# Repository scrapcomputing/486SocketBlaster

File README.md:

# Go back to the main branch. [Theres nothing to see here.](https://youtu.be/NuAKnbIr6TE)

# 486SocketBlaster

486SocketBlaster is a simple voltage adapter for 486 processors. It allows you
to use a 3-volt 486 CPU on an older 5-volt-only motherboard. For example you
can use a DX4 or an Am5x86 on an old 486 motherboard that would normally only
work with 5-volt CPUs. This basically converts any 3-volt CPU to an "Overdrive".

# How does it work ?

It is really simple: All CPU pins are passed through to the motherboard socket,
except for the Vcc. Those are connected to the output of a mini buck converter
that can be soldered to the 486SocketBlaster board.

# Soldering/Assembly Instructions

This board is not the easiest thing to solder, but can be done with a standard
soldering iron and some patience.
The best way to solder the headers is to start with the innermost one and work
outwards in a spiral manner alternating between the top and bottom side as
needed (see image below). This way you only work on the outside and can easily
reach all the pins.

A desoldering gun may be useful when you accidentally clog up other holes. But
it is probably best to be very careful and avoid clogging them in the first
place. Also using flux makes it easier.

Please make sure you check the solder joints (also check for continuity) before
you add another row of headers on the same side, because the new row will
permanently block your access to the solder joints!
Desoldering a header is almost impossible even with a desoldering gun due to the
very tight hole tolerances.
So it has to be soldered correctly from the first try.

# Voltage regulator

The 486SocketBlaster can be powered by a cheap of-the-shelf buck converter, or
by an external one. The circuit board accepts two common types of small voltage
buck converters, usually found using keywords like "mini buck converter".
These are commonly rated at up to 3A of current. Given that 3-volt 486 CPUs are
usually very efficient (the DX4-100 is rated at max 3.55/5.22W typical/max) such
a regulator should be adequate in most cases.
For best stability try to source a good quality part.

If you are planning to overclock or to use a more power hungry CPU, please use an external regulation circuit plugged in to the `ExtPwr` header, or use a *very* good quality mini buck converter.

# WARNING!!!

Please make sure you know what you are doing!
Improper assembly/settings/use can damage both your precious motherboard and your precious CPU!

# Features

- External Power Header. This can be used either for monitoring the CPU voltage, or for providing power externally, either with an external power supply or an external voltage regulator.
- CLKMUL Header for selecting/overriding the CPU multiplier. This controls CPU pin `R17`. 1-2 connects it to the motherboard socket pin and 2-3 connects it to ground. This reduces the multiplier of a DX4 to 2x (66MHz) and sets the multiplier of an Am5x86 to 4x (133MHz).
- WB/WT Header for selecting/overriding Write-Back/Write-Through cache. This controls processor CPU pin `B13` (which is the `CLKMUL` pin in earlier 486 CPUs). 1-2 connects it to the motherboard socket pin, and 2-3 connects it to Vcc, which enables Write-Back.

# Bill of materials

Item                            | ##  | Description
--------------------------------|-----|--------------------------------------------------------
mini buck converter             | 1   | We support two common sizes: 22x17mm and 18x12mm. These usually have chips like MP1584, MP2307 and others
40pin SIP pin header (male)     | 5   | Single-row round pin 2.54mm pitch (male). Socket pin diameter: 0.50mm, PCB pin diameter: 0.60mm. (see photo below)
40pin SIP socket header (female)| 5   | Single-row round pin sockets, 2.54mm pitch. PCB pin diameter: 0.55mm. (see photo below) 
SMD Ceramic Capacitors          | 4   | 10uF SMD 1206, 6.3V or higher
Through-hole Capacitor          | 1   | 10uF ceramic through-hole capacitor, 6.3V or higher
3-pin header 2.54mm pitch       | 2   | (optional) Headers used for selecting the CPU Multiplier (CLKMUL) and Write-Back/Write-Through cache (WB/WT)
Jumper 2.54mm pitch             | 2   | (optional) Jumpers for the CLKMUL and WB/WT headers

Gerber files can be found in the releases: https://github.com/scrapcomputing/486SocketBlaster/releases

Please note that the headers are a very tight fit. So please make sure that you get headers of the correct pin diameter.

With the limited testing I have done so far, it seems that you need at least
one 10uF through-hole ceramic capacitor, otherwise the voltage ripple is too
high and the system can become unstable with a DX4 @ 100MHz, using a cheap
MP1584-based buck converter.

# Videos featuring the 486 Socket Blaster
- Original video with rev0.1 PCB (part 1): https://www.youtube.com/watch?v=n5qlx4qKbSE
- Rev0.2 PCB and trying out smoothing caps (part 2): https://www.youtube.com/watch?v=7anzRWXtba0
- Choosing capacitor values for a 5x86 (part 3): https://www.youtube.com/watch?v=CLPSJ0jOQsU
- Detailed assembly instructions by Epictronics (rev 0.4 PCB): https://www.youtube.com/watch?v=vEpAoVE4KjU

# Changelist
- Rev 0.5 : Adds WB/WT header and fixes CLKMUL table silkscreen for am5x86.
- Rev 0.4 : Larger holes for the female headers (0.62mm instead of 0.57mm). These should fit headers with 0.55mm pin diameter.
- Rev 0.3 : Updates silk screen for larger capacitor values and fixes CLKMUL table.
- Rev 0.2 : Fixes initial revision bugs.

# List of other similar 486 adapter projects
- With an onboard voltage regulator: https://github.com/LimeProgramming/486SocketBlaster/tree/4-layer-onboard-regulator

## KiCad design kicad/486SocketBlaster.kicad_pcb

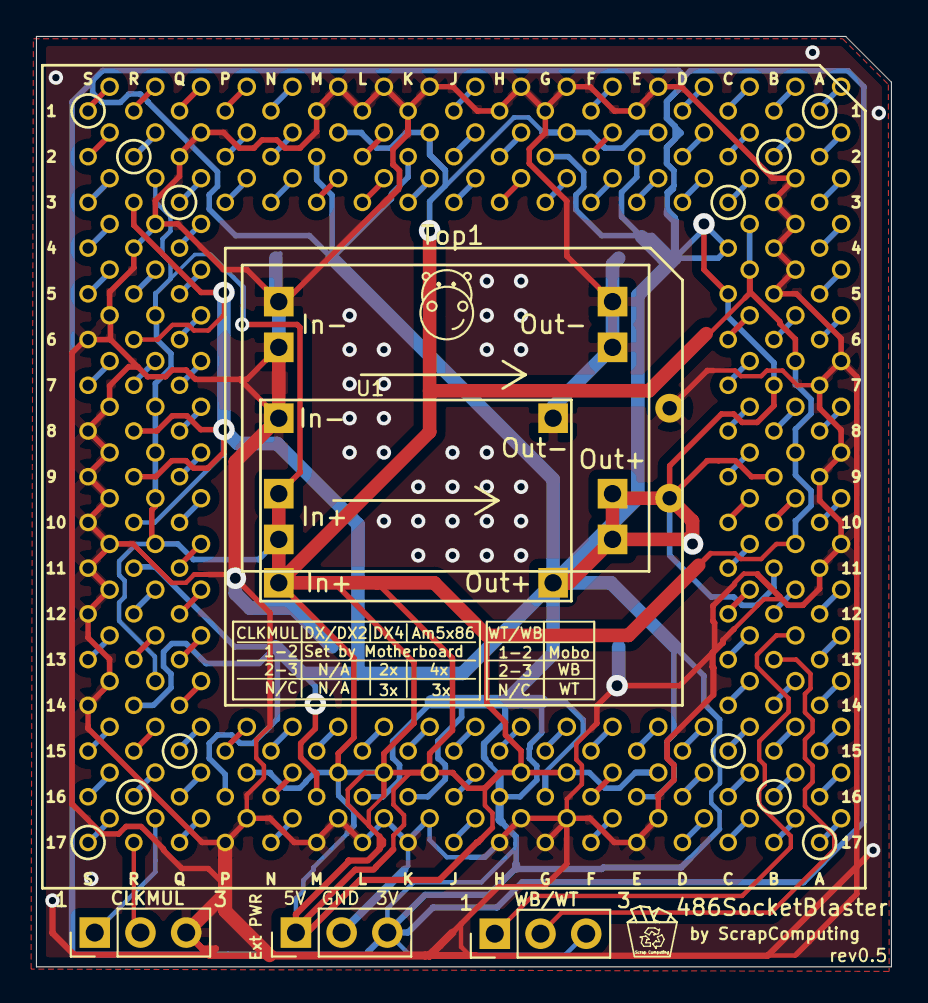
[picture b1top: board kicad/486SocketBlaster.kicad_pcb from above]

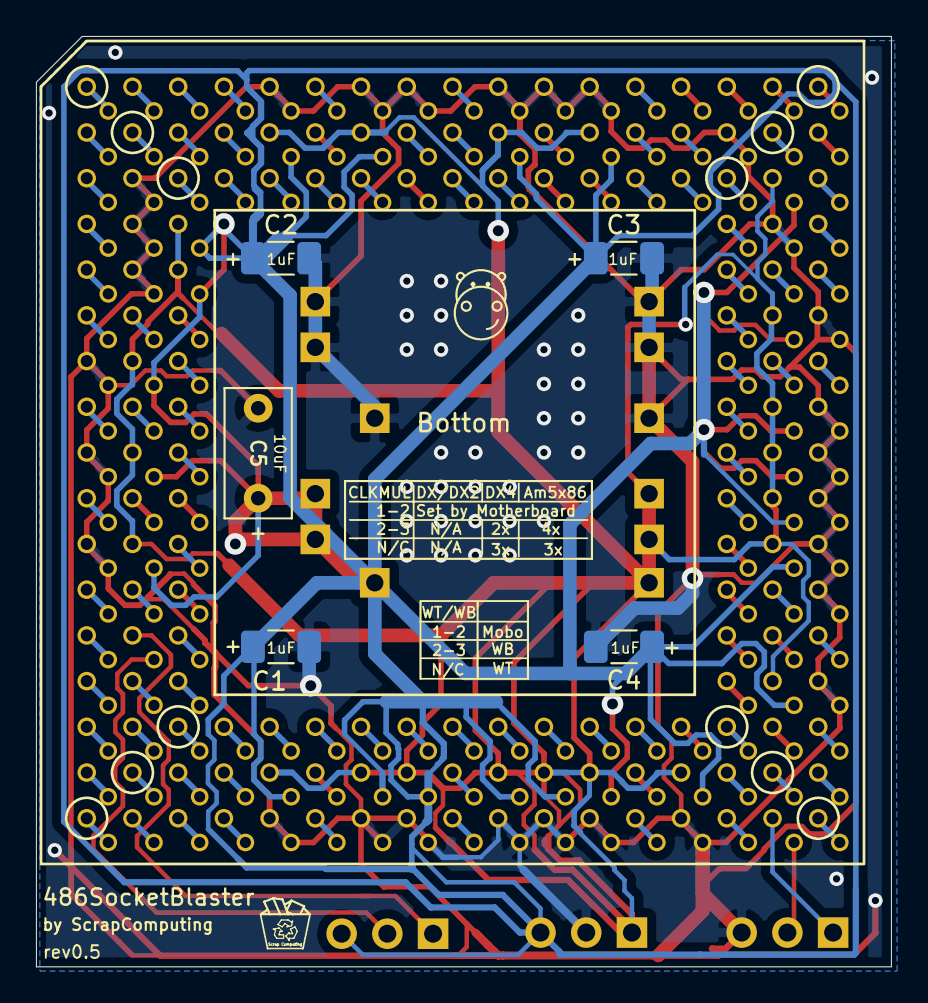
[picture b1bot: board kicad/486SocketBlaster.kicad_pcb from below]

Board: 2 copper layers, 47.5 x 51.7 mm, 12 parts (5 on the bottom side), 122 nets.

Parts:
Bot1: 486; 486_168pga
C1, C2, C3, C4: 10uF; C_1206_3216Metric_Pad1.33x1.80mm_HandSolder
C5: 10uF; C_Rect_L7.0mm_W3.5mm_P5.00mm
CLKMUL: CLKMUL; PinHeader_1x03_P2.54mm_Vertical
ExtPwr1: Conn_01x03; PinHeader_1x03_P2.54mm_Vertical
J1: Conn_01x03; PinHeader_1x03_P2.54mm_Vertical
Top1: 486; 486_168pga_socket
U1: VoltageRegulator; VoltageRegulator2
U3: VoltageRegulator

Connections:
GND: Bot1.A7, Bot1.A9, Bot1.A11, Bot1.B3, Bot1.B4, Bot1.B5, Bot1.E1, Bot1.E17, Bot1.G1, Bot1.G17, Bot1.H1, Bot1.H17, Bot1.K1, Bot1.K17, Bot1.L1, Bot1.L17, Bot1.M1, Bot1.M17, Bot1.P17, Bot1.Q2, Bot1.R4, Bot1.S6, Bot1.S8, Bot1.S9, Bot1.S10, Bot1.S11, Bot1.S12, Bot1.S14, C1.2, C2.2, C3.2, C4.2, C5.2, CLKMUL.3, ExtPwr1.2, Top1.A7, Top1.A9, Top1.A11, Top1.B3, Top1.B4, Top1.B5, Top1.E1, Top1.E17, Top1.G1, Top1.G17, Top1.H1, Top1.H17, Top1.K1, Top1.K17, Top1.L1, Top1.L17, Top1.M1, Top1.M17, Top1.P17, Top1.Q2, Top1.R4, Top1.S6, Top1.S8, Top1.S9, Top1.S10, Top1.S11, Top1.S12, Top1.S14, U1.GNDin, U1.GNDout, U3.GNDin, U3.GNDout
unnamed: Bot1.A1, Top1.A1
unnamed: Bot1.A2, Top1.A2
unnamed: Bot1.A3, Top1.A3
unnamed: Bot1.A4, Top1.A4
unnamed: Bot1.A5, Top1.A5
unnamed: Bot1.A6, Top1.A6
unnamed: Bot1.A8, Top1.A8
unnamed: Bot1.A10, Top1.A10
unnamed: Bot1.A12, Top1.A12
unnamed: Bot1.A13, Top1.A13
unnamed: Bot1.A14, Top1.A14
unnamed: Bot1.A15, Top1.A15
unnamed: Bot1.A16, Top1.A16
unnamed: Bot1.A17, Top1.A17
unnamed: Bot1.B1, Top1.B1
unnamed: Bot1.B2, Top1.B2
unnamed: Bot1.B6, Top1.B6
unnamed: Bot1.B8, Top1.B8
unnamed: Bot1.B10, Top1.B10
unnamed: Bot1.B7, Bot1.B9, Bot1.B11, Bot1.C4, Bot1.C5, Bot1.E2, Bot1.E16, Bot1.G2, Bot1.G16, Bot1.H16, Bot1.K2, Bot1.K16, Bot1.L16, Bot1.M2, Bot1.M16, Bot1.P16, Bot1.R3, Bot1.R6, Bot1.R8, Bot1.R9, Bot1.R10, Bot1.R11, Bot1.R14, ExtPwr1.1, U1.Vin, U3.Vin
unnamed: Bot1.B12, Top1.B12
unnamed: Bot1.B13, J1.1
unnamed: Bot1.B14, Top1.B14
unnamed: Bot1.B15, Top1.B15
unnamed: Bot1.B16, Top1.B16
unnamed: Bot1.B17, Top1.B17
unnamed: Bot1.C1, Top1.C1
unnamed: Bot1.C2, Top1.C2
unnamed: Bot1.C3, Top1.C3
unnamed: Bot1.C6, Top1.C6
unnamed: Bot1.C7, Top1.C7
unnamed: Bot1.C8, Top1.C8
unnamed: Bot1.C9, Top1.C9
unnamed: Bot1.C10, Top1.C10
unnamed: Bot1.C11, Top1.C11
unnamed: Bot1.C12, Top1.C12
unnamed: Bot1.C13, Top1.C13
unnamed: Bot1.C14, Top1.C14
unnamed: Bot1.C15, Top1.C15
unnamed: Bot1.C16, Top1.C16
unnamed: Bot1.C17, Top1.C17
unnamed: Bot1.D1, Top1.D1
unnamed: Bot1.D2, Top1.D2
unnamed: Bot1.D3, Top1.D3
unnamed: Bot1.D15, Top1.D15
unnamed: Bot1.D16, Top1.D16
unnamed: Bot1.D17, Top1.D17
unnamed: Bot1.E3, Top1.E3
unnamed: Bot1.E15, Top1.E15
unnamed: Bot1.F1, Top1.F1
unnamed: Bot1.F2, Top1.F2
unnamed: Bot1.F3, Top1.F3
unnamed: Bot1.F15, Top1.F15
unnamed: Bot1.F16, Top1.F16
unnamed: Bot1.F17, Top1.F17
unnamed: Bot1.G3, Top1.G3
unnamed: Bot1.G15, Top1.G15
unnamed: Bot1.H2, Top1.H2
unnamed: Bot1.H3, Top1.H3
unnamed: Bot1.H15, Top1.H15
unnamed: Bot1.J1, Top1.J1
unnamed: Bot1.J2, Top1.J2
unnamed: Bot1.J3, Top1.J3
unnamed: Bot1.J15, Top1.J15
unnamed: Bot1.J16, Top1.J16
unnamed: Bot1.J17, Top1.J17
unnamed: Bot1.K3, Top1.K3
unnamed: Bot1.K15, Top1.K15
unnamed: Bot1.L2, Top1.L2
unnamed: Bot1.L3, Top1.L3
unnamed: Bot1.L15, Top1.L15
unnamed: Bot1.M3, Top1.M3
unnamed: Bot1.M15, Top1.M15
unnamed: Bot1.N1, Top1.N1
unnamed: Bot1.N2, Top1.N2
unnamed: Bot1.N3, Top1.N3
unnamed: Bot1.N15, Top1.N15
unnamed: Bot1.N16, Top1.N16
unnamed: Bot1.N17, Top1.N17
unnamed: Bot1.P1, Top1.P1
unnamed: Bot1.P2, Top1.P2
unnamed: Bot1.P3, Top1.P3
unnamed: Bot1.P15, Top1.P15
unnamed: Bot1.Q1, Top1.Q1
unnamed: Bot1.Q3, Top1.Q3
unnamed: Bot1.Q4, Top1.Q4
unnamed: Bot1.Q5, Top1.Q5
unnamed: Bot1.Q6, Top1.Q6
unnamed: Bot1.Q7, Top1.Q7
unnamed: Bot1.Q8, Top1.Q8
unnamed: Bot1.Q9, Top1.Q9
unnamed: Bot1.Q10, Top1.Q10
unnamed: Bot1.Q11, Top1.Q11
unnamed: Bot1.Q12, Top1.Q12
unnamed: Bot1.Q13, Top1.Q13
unnamed: Bot1.Q14, Top1.Q14
unnamed: Bot1.Q15, Top1.Q15
unnamed: Bot1.Q16, Top1.Q16
unnamed: Bot1.Q17, Top1.Q17
unnamed: Bot1.R1, Top1.R1
unnamed: Bot1.R2, Top1.R2
unnamed: Bot1.R5, Top1.R5
unnamed: Bot1.R7, Top1.R7
unnamed: Bot1.R12, Top1.R12
unnamed: Bot1.R13, Top1.R13
unnamed: Bot1.R15, Top1.R15
unnamed: Bot1.R16, Top1.R16
unnamed: Bot1.R17, CLKMUL.1
unnamed: Bot1.S1, Top1.S1
unnamed: Bot1.S2, Top1.S2
unnamed: Bot1.S3, Top1.S3
unnamed: Bot1.S4, Top1.S4
unnamed: Bot1.S5, Top1.S5
unnamed: Bot1.S7, Top1.S7
unnamed: Bot1.S13, Top1.S13
unnamed: Bot1.S15, Top1.S15
unnamed: Bot1.S16, Top1.S16
unnamed: Bot1.S17, Top1.S17
unnamed: C1.1, C2.1, C3.1, C4.1, C5.1, ExtPwr1.3, J1.3, Top1.B7, Top1.B9, Top1.B11, Top1.C4, Top1.C5, Top1.E2, Top1.E16, Top1.G2, Top1.G16, Top1.H16, Top1.K2, Top1.K16, Top1.L16, Top1.M2, Top1.M16, Top1.P16, Top1.R3, Top1.R6, Top1.R8, Top1.R9, Top1.R10, Top1.R11, Top1.R14, U1.Vout, U3.Vout
unnamed: CLKMUL.2, Top1.R17
unnamed: J1.2, Top1.B13

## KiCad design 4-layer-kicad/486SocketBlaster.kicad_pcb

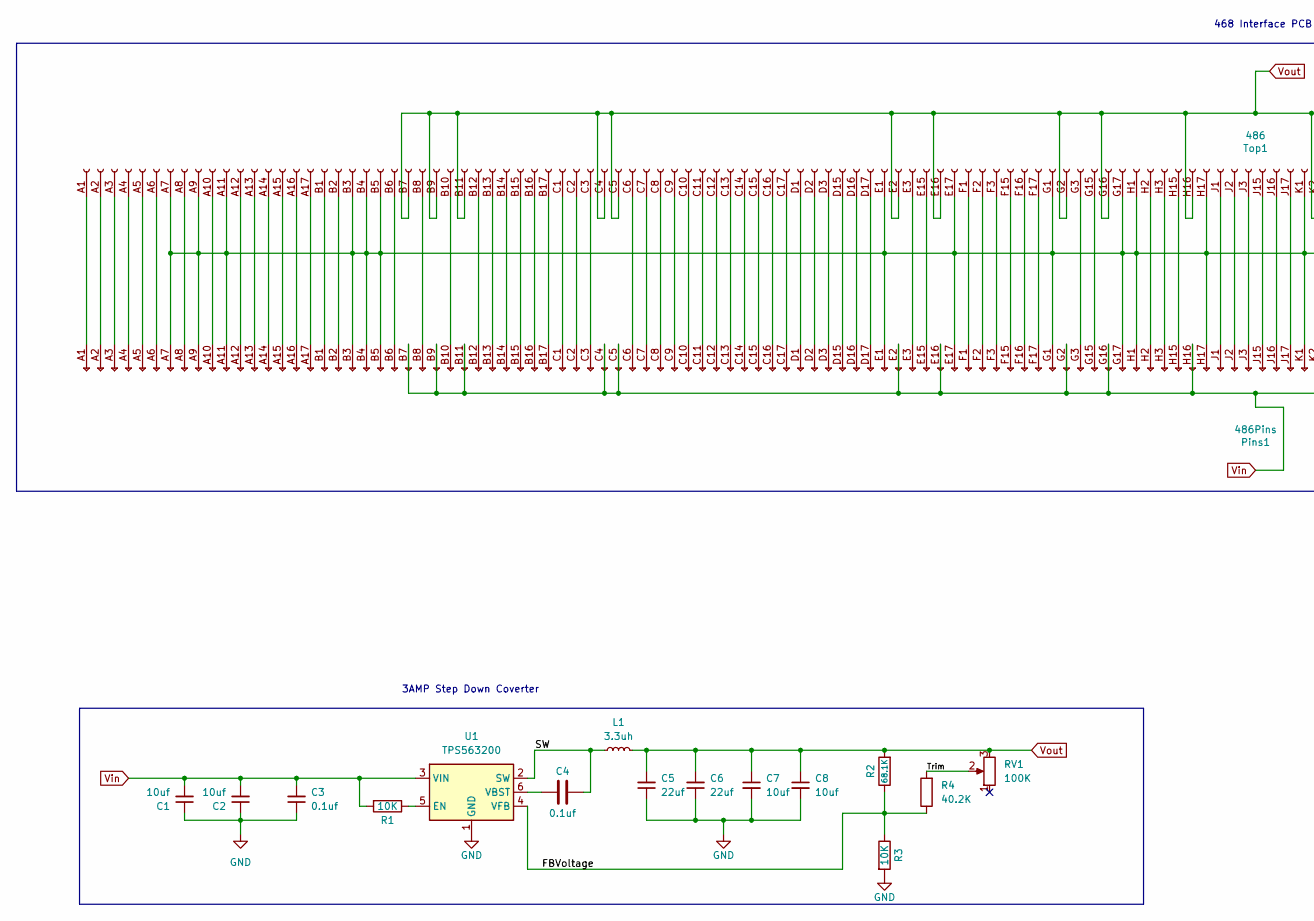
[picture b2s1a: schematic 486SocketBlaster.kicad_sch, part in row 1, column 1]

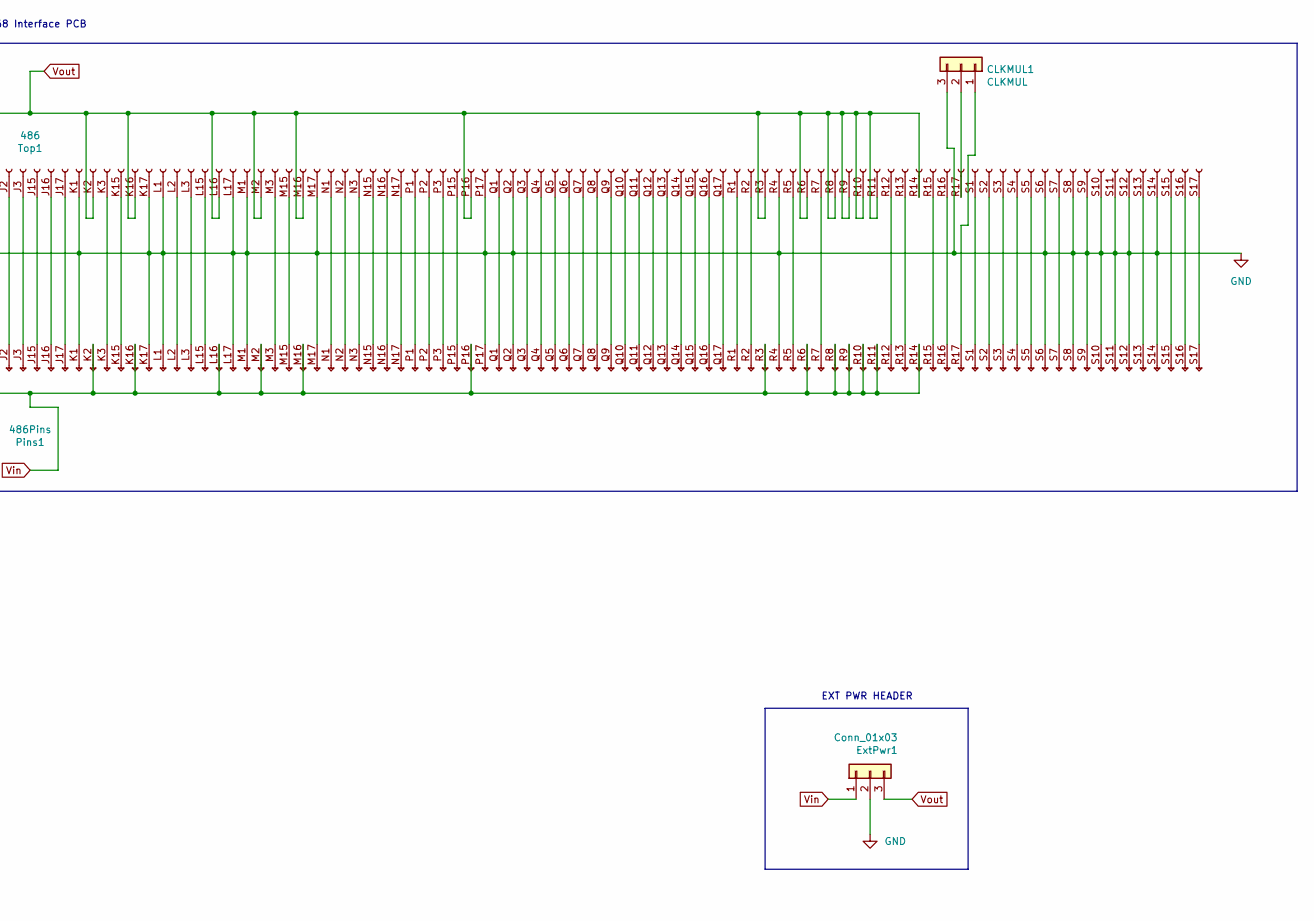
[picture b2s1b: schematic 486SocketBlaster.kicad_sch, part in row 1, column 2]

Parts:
C1, C2: 10uf; C_0805_2012Metric; JLCPCB C15850
C3, C4: 0.1uf; C_0805_2012Metric; JLCPCB C28233
C5, C6: 22uf; C_1206_3216Metric; JLCPCB C12891
C7, C8: 10uf; C_0805_2012Metric; JLCPCB C12891
CLKMUL1: CLKMUL; PinHeader_1x03_P2.54mm_Vertical
ExtPwr1: Conn_01x03; PinHeader_1x03_P2.54mm_Vertical
L1: 3.3uh; L_5.5x5.5; JLCPCB C436534
Pins1: 486Pins; 486_168pga_pins
R1, R3: 10K; R_0603_1608Metric; JLCPCB C25804
R2: 68.1K; R_0603_1608Metric; JLCPCB for set C4216
R4: 40.2K; R_0603_1608Metric; JLCPCB for ADJ C12447
RV1: 100K; tinySMDpot
Top1: 486; 486_168pga_socket
U1: TPS563200; SOT-23-6; LCSC C97253

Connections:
/FBVoltage: R2.1, R3.1, R4.1, U1.4 (VFB)
/SW: C4.2, L1.1, U1.2 (SW)
/Trim: R4.2, RV1.2
GND: C1.1, C2.1, C3.1, C5.1, C6.1, C7.2, C8.2, CLKMUL1.3, ExtPwr1.2, Pins1.A7 (Pin_7), Pins1.A9 (Pin_9), Pins1.A11 (Pin_11), Pins1.B3 (Pin_3), Pins1.B4 (Pin_4), Pins1.B5 (Pin_5), Pins1.E1 (Pin_1), Pins1.E17 (Pin_17), Pins1.G1 (Pin_1), Pins1.G17 (Pin_17), Pins1.H1 (Pin_1), Pins1.H17 (Pin_17), Pins1.K1 (Pin_1), Pins1.K17 (Pin_17), Pins1.L1 (Pin_1), Pins1.L17 (Pin_17), Pins1.M1 (Pin_1), Pins1.M17 (Pin_17), Pins1.P17 (Pin_17), Pins1.Q2 (Pin_2), Pins1.R4 (Pin_4), Pins1.S6 (Pin_6), Pins1.S8 (Pin_8), Pins1.S9 (Pin_9), Pins1.S10 (Pin_10), Pins1.S11 (Pin_11), Pins1.S12 (Pin_12), Pins1.S14 (Pin_14), R3.2, Top1.A7 (Pin_7), Top1.A9 (Pin_9), Top1.A11 (Pin_11), Top1.B3 (Pin_3), Top1.B4 (Pin_4), Top1.B5 (Pin_5), Top1.E1 (Pin_1), Top1.E17 (Pin_17), Top1.G1 (Pin_1), Top1.G17 (Pin_17), Top1.H1 (Pin_1), Top1.H17 (Pin_17), Top1.K1 (Pin_1), Top1.K17 (Pin_17), Top1.L1 (Pin_1), Top1.L17 (Pin_17), Top1.M1 (Pin_1), Top1.M17 (Pin_17), Top1.P17 (Pin_17), Top1.Q2 (Pin_2), Top1.R4 (Pin_4), Top1.S6 (Pin_6), Top1.S8 (Pin_8), Top1.S9 (Pin_9), Top1.S10 (Pin_10), Top1.S11 (Pin_11), Top1.S12 (Pin_12), Top1.S14 (Pin_14), U1.1 (GND)
unnamed: C4.1, U1.6 (VBST)
unnamed: CLKMUL1.1, Pins1.R17 (Pin_17)
unnamed: CLKMUL1.2, Top1.R17 (Pin_17)
unnamed: Pins1.A1 (Pin_1), Top1.A1 (Pin_1)
unnamed: Pins1.A2 (Pin_2), Top1.A2 (Pin_2)
unnamed: Pins1.A3 (Pin_3), Top1.A3 (Pin_3)
unnamed: Pins1.A4 (Pin_4), Top1.A4 (Pin_4)
unnamed: Pins1.A5 (Pin_5), Top1.A5 (Pin_5)
unnamed: Pins1.A6 (Pin_6), Top1.A6 (Pin_6)
unnamed: Pins1.A8 (Pin_8), Top1.A8 (Pin_8)
unnamed: Pins1.A10 (Pin_10), Top1.A10 (Pin_10)
unnamed: Pins1.A12 (Pin_12), Top1.A12 (Pin_12)
unnamed: Pins1.A13 (Pin_13), Top1.A13 (Pin_13)
unnamed: Pins1.A14 (Pin_14), Top1.A14 (Pin_14)
unnamed: Pins1.A15 (Pin_15), Top1.A15 (Pin_15)
unnamed: Pins1.A16 (Pin_16), Top1.A16 (Pin_16)
unnamed: Pins1.A17 (Pin_17), Top1.A17 (Pin_17)
unnamed: Pins1.B1 (Pin_1), Top1.B1 (Pin_1)
unnamed: Pins1.B2 (Pin_2), Top1.B2 (Pin_2)
unnamed: Pins1.B6 (Pin_6), Top1.B6 (Pin_6)
unnamed: Pins1.B8 (Pin_8), Top1.B8 (Pin_8)
unnamed: Pins1.B10 (Pin_10), Top1.B10 (Pin_10)
unnamed: Pins1.B12 (Pin_12), Top1.B12 (Pin_12)
unnamed: Pins1.B13 (Pin_13), Top1.B13 (Pin_13)
unnamed: Pins1.B14 (Pin_14), Top1.B14 (Pin_14)
unnamed: Pins1.B15 (Pin_15), Top1.B15 (Pin_15)
unnamed: Pins1.B16 (Pin_16), Top1.B16 (Pin_16)
unnamed: Pins1.B17 (Pin_17), Top1.B17 (Pin_17)
unnamed: Pins1.C1 (Pin_1), Top1.C1 (Pin_1)
unnamed: Pins1.C2 (Pin_2), Top1.C2 (Pin_2)
unnamed: Pins1.C3 (Pin_3), Top1.C3 (Pin_3)
unnamed: Pins1.C6 (Pin_6), Top1.C6 (Pin_6)
unnamed: Pins1.C7 (Pin_7), Top1.C7 (Pin_7)
unnamed: Pins1.C8 (Pin_8), Top1.C8 (Pin_8)
unnamed: Pins1.C9 (Pin_9), Top1.C9 (Pin_9)
unnamed: Pins1.C10 (Pin_10), Top1.C10 (Pin_10)
unnamed: Pins1.C11 (Pin_11), Top1.C11 (Pin_11)
unnamed: Pins1.C12 (Pin_12), Top1.C12 (Pin_12)
unnamed: Pins1.C13 (Pin_13), Top1.C13 (Pin_13)
unnamed: Pins1.C14 (Pin_14), Top1.C14 (Pin_14)
unnamed: Pins1.C15 (Pin_15), Top1.C15 (Pin_15)
unnamed: Pins1.C16 (Pin_16), Top1.C16 (Pin_16)
unnamed: Pins1.C17 (Pin_17), Top1.C17 (Pin_17)
unnamed: Pins1.D1 (Pin_1), Top1.D1 (Pin_1)
unnamed: Pins1.D2 (Pin_2), Top1.D2 (Pin_2)
unnamed: Pins1.D3 (Pin_3), Top1.D3 (Pin_3)
unnamed: Pins1.D15 (Pin_15), Top1.D15 (Pin_15)
unnamed: Pins1.D16 (Pin_16), Top1.D16 (Pin_16)
unnamed: Pins1.D17 (Pin_17), Top1.D17 (Pin_17)
unnamed: Pins1.E3 (Pin_3), Top1.E3 (Pin_3)
unnamed: Pins1.E15 (Pin_15), Top1.E15 (Pin_15)
unnamed: Pins1.F1 (Pin_1), Top1.F1 (Pin_1)
unnamed: Pins1.F2 (Pin_2), Top1.F2 (Pin_2)
unnamed: Pins1.F3 (Pin_3), Top1.F3 (Pin_3)
unnamed: Pins1.F15 (Pin_15), Top1.F15 (Pin_15)
unnamed: Pins1.F16 (Pin_16), Top1.F16 (Pin_16)
unnamed: Pins1.F17 (Pin_17), Top1.F17 (Pin_17)
unnamed: Pins1.G3 (Pin_3), Top1.G3 (Pin_3)
unnamed: Pins1.G15 (Pin_15), Top1.G15 (Pin_15)
unnamed: Pins1.H2 (Pin_2), Top1.H2 (Pin_2)
unnamed: Pins1.H3 (Pin_3), Top1.H3 (Pin_3)
unnamed: Pins1.H15 (Pin_15), Top1.H15 (Pin_15)
unnamed: Pins1.J1 (Pin_1), Top1.J1 (Pin_1)
unnamed: Pins1.J2 (Pin_2), Top1.J2 (Pin_2)
unnamed: Pins1.J3 (Pin_3), Top1.J3 (Pin_3)
unnamed: Pins1.J15 (Pin_15), Top1.J15 (Pin_15)
unnamed: Pins1.J16 (Pin_16), Top1.J16 (Pin_16)
unnamed: Pins1.J17 (Pin_17), Top1.J17 (Pin_17)
unnamed: Pins1.K3 (Pin_3), Top1.K3 (Pin_3)
unnamed: Pins1.K15 (Pin_15), Top1.K15 (Pin_15)
unnamed: Pins1.L2 (Pin_2), Top1.L2 (Pin_2)
unnamed: Pins1.L3 (Pin_3), Top1.L3 (Pin_3)
unnamed: Pins1.L15 (Pin_15), Top1.L15 (Pin_15)
unnamed: Pins1.M3 (Pin_3), Top1.M3 (Pin_3)
unnamed: Pins1.M15 (Pin_15), Top1.M15 (Pin_15)
unnamed: Pins1.N1 (Pin_1), Top1.N1 (Pin_1)
unnamed: Pins1.N2 (Pin_2), Top1.N2 (Pin_2)
unnamed: Pins1.N3 (Pin_3), Top1.N3 (Pin_3)
unnamed: Pins1.N15 (Pin_15), Top1.N15 (Pin_15)
unnamed: Pins1.N16 (Pin_16), Top1.N16 (Pin_16)
unnamed: Pins1.N17 (Pin_17), Top1.N17 (Pin_17)
unnamed: Pins1.P1 (Pin_1), Top1.P1 (Pin_1)
unnamed: Pins1.P2 (Pin_2), Top1.P2 (Pin_2)
unnamed: Pins1.P3 (Pin_3), Top1.P3 (Pin_3)
unnamed: Pins1.P15 (Pin_15), Top1.P15 (Pin_15)
unnamed: Pins1.Q1 (Pin_1), Top1.Q1 (Pin_1)
unnamed: Pins1.Q3 (Pin_3), Top1.Q3 (Pin_3)
unnamed: Pins1.Q4 (Pin_4), Top1.Q4 (Pin_4)
unnamed: Pins1.Q5 (Pin_5), Top1.Q5 (Pin_5)
unnamed: Pins1.Q6 (Pin_6), Top1.Q6 (Pin_6)
unnamed: Pins1.Q7 (Pin_7), Top1.Q7 (Pin_7)
unnamed: Pins1.Q8 (Pin_8), Top1.Q8 (Pin_8)
unnamed: Pins1.Q9 (Pin_9), Top1.Q9 (Pin_9)
unnamed: Pins1.Q10 (Pin_10), Top1.Q10 (Pin_10)
unnamed: Pins1.Q11 (Pin_11), Top1.Q11 (Pin_11)
unnamed: Pins1.Q12 (Pin_12), Top1.Q12 (Pin_12)
unnamed: Pins1.Q13 (Pin_13), Top1.Q13 (Pin_13)
unnamed: Pins1.Q14 (Pin_14), Top1.Q14 (Pin_14)
unnamed: Pins1.Q15 (Pin_15), Top1.Q15 (Pin_15)
unnamed: Pins1.Q16 (Pin_16), Top1.Q16 (Pin_16)
unnamed: Pins1.Q17 (Pin_17), Top1.Q17 (Pin_17)
unnamed: Pins1.R1 (Pin_1), Top1.R1 (Pin_1)
unnamed: Pins1.R2 (Pin_2), Top1.R2 (Pin_2)
unnamed: Pins1.R5 (Pin_5), Top1.R5 (Pin_5)
unnamed: Pins1.R7 (Pin_7), Top1.R7 (Pin_7)
unnamed: Pins1.R12 (Pin_12), Top1.R12 (Pin_12)
unnamed: Pins1.R13 (Pin_13), Top1.R13 (Pin_13)
unnamed: Pins1.R15 (Pin_15), Top1.R15 (Pin_15)
unnamed: Pins1.R16 (Pin_16), Top1.R16 (Pin_16)
unnamed: Pins1.S1 (Pin_1), Top1.S1 (Pin_1)
unnamed: Pins1.S2 (Pin_2), Top1.S2 (Pin_2)
unnamed: Pins1.S3 (Pin_3), Top1.S3 (Pin_3)
unnamed: Pins1.S4 (Pin_4), Top1.S4 (Pin_4)
unnamed: Pins1.S5 (Pin_5), Top1.S5 (Pin_5)
unnamed: Pins1.S7 (Pin_7), Top1.S7 (Pin_7)
unnamed: Pins1.S13 (Pin_13), Top1.S13 (Pin_13)
unnamed: Pins1.S15 (Pin_15), Top1.S15 (Pin_15)
unnamed: Pins1.S16 (Pin_16), Top1.S16 (Pin_16)
unnamed: Pins1.S17 (Pin_17), Top1.S17 (Pin_17)
unnamed: R1.1, U1.5 (EN)
Vin: C1.2, C2.2, C3.2, ExtPwr1.1, Pins1.B7 (Pin_7), Pins1.B9 (Pin_9), Pins1.B11 (Pin_11), Pins1.C4 (Pin_4), Pins1.C5 (Pin_5), Pins1.E2 (Pin_2), Pins1.E16 (Pin_16), Pins1.G2 (Pin_2), Pins1.G16 (Pin_16), Pins1.H16 (Pin_16), Pins1.K2 (Pin_2), Pins1.K16 (Pin_16), Pins1.L16 (Pin_16), Pins1.M2 (Pin_2), Pins1.M16 (Pin_16), Pins1.P16 (Pin_16), Pins1.R3 (Pin_3), Pins1.R6 (Pin_6), Pins1.R8 (Pin_8), Pins1.R9 (Pin_9), Pins1.R10 (Pin_10), Pins1.R11 (Pin_11), Pins1.R14 (Pin_14), R1.2, U1.3 (VIN)
Vout: C5.2, C6.2, C7.1, C8.1, ExtPwr1.3, L1.2, R2.2, RV1.3, Top1.B7 (Pin_7), Top1.B9 (Pin_9), Top1.B11 (Pin_11), Top1.C4 (Pin_4), Top1.C5 (Pin_5), Top1.E2 (Pin_2), Top1.E16 (Pin_16), Top1.G2 (Pin_2), Top1.G16 (Pin_16), Top1.H16 (Pin_16), Top1.K2 (Pin_2), Top1.K16 (Pin_16), Top1.L16 (Pin_16), Top1.M2 (Pin_2), Top1.M16 (Pin_16), Top1.P16 (Pin_16), Top1.R3 (Pin_3), Top1.R6 (Pin_6), Top1.R8 (Pin_8), Top1.R9 (Pin_9), Top1.R10 (Pin_10), Top1.R11 (Pin_11), Top1.R14 (Pin_14)

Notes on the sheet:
468 Interface PCB
EXT PWR HEADER
3AMP Step Down Coverter

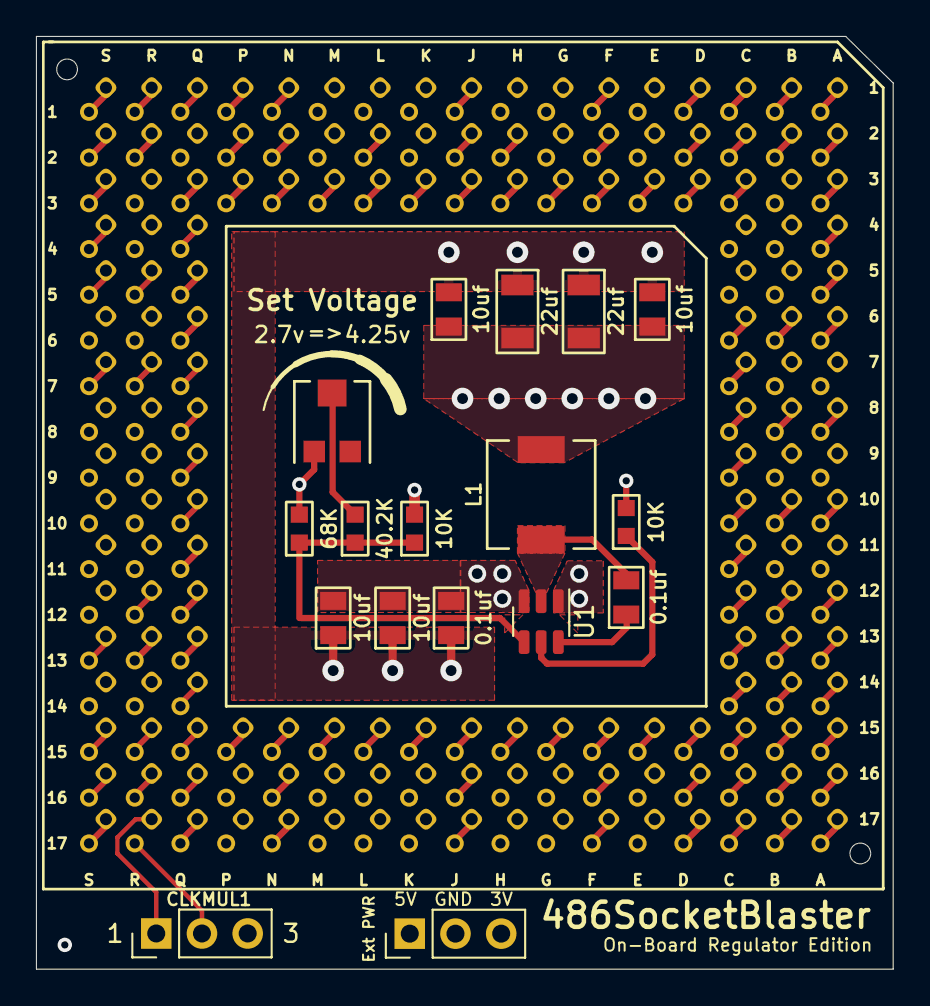
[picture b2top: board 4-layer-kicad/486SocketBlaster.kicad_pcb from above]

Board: 4 copper layers, 47.6 x 51.8 mm, 19 parts (0 on the bottom side), 126 nets.

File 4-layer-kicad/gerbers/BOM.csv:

Designator,Footprint,Quantity,Value,LCSC Part #,JLCPCB
R3,R_0603_1608Metric,1,10K,,C25804
C5,C_1206_3216Metric,1,22uf,,C12891
C6,C_1206_3216Metric,1,22uf,,C12891
R1,R_0603_1608Metric,1,10K,,C25804
U1,SOT-23-6,1,TPS563200,C97253,C97253
C3,C_0603_1608Metric,1,0.1uf,,C28233
C2,C_0805_2012Metric,1,10uf,,C15850
C7,CP_EIA-3216-12_Kemet-S_Pad1.58x1.35mm_HandSolder,1,47uf,,C688949
R2,R_0603_1608Metric,1,68.1K,,C25976
L1,L_5.5x5.5,1,3.3uh,,C436534
R4,R_0603_1608Metric,1,40.2K,,C12447
C1,C_0805_2012Metric,1,10uf,,C15850
C4,C_0603_1608Metric,1,0.1uf,,C28233

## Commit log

2022-12-30 Rev 0.2: Fixes initial revision bugs
    - Supports second type of voltage regulator
    - Hole pads are now a little larger
2022-12-31 README: Improved assembly instructions
2023-01-09 Fixed CPUMUL multipliers table and changed capacitor values to 10uF
2023-01-09 Updated capacitor values in README
2023-01-10 upload kicad files
2023-01-10 fixed tant cap
2023-01-13 Upload original kicad files
2023-01-13 Upload Kicad with regulator
2023-01-14 4layerPCB images
2023-01-14 Create 4layer-kicad
2023-01-14 upload 4 layer PCB
2023-01-14 uploading 4 layer kicad
2023-01-14 Add files via upload
    gerbers
2023-01-14 added BOM + CPL files for JLCPCB SMT service
2023-01-14 update
    might have forgotten to save before uploading in the first place, who knows
2023-01-14 Added missing files
2023-01-17 Add list of projects
2023-02-05 added gerbers
2023-02-14 Larger holes (and pads) for 0.55mm female pin headers.
2023-04-23 Added link to gerber files
2023-05-02 update
    +larger drill holes for socket
    +Replaced 68.1K with 68K resistor, one less extended part from jlc
    +updated gerbers, Bom & CPL
2023-05-13 Adds links to videos
2023-06-25 Rev 0.5: Add WB/WT header and fix CLKMUL table silkscreen for am5x86
